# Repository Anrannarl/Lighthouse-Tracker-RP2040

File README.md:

# Lighthouse-Tracker-RP2040
A Lighthouse tracker based on Raspberry Pi Pico.

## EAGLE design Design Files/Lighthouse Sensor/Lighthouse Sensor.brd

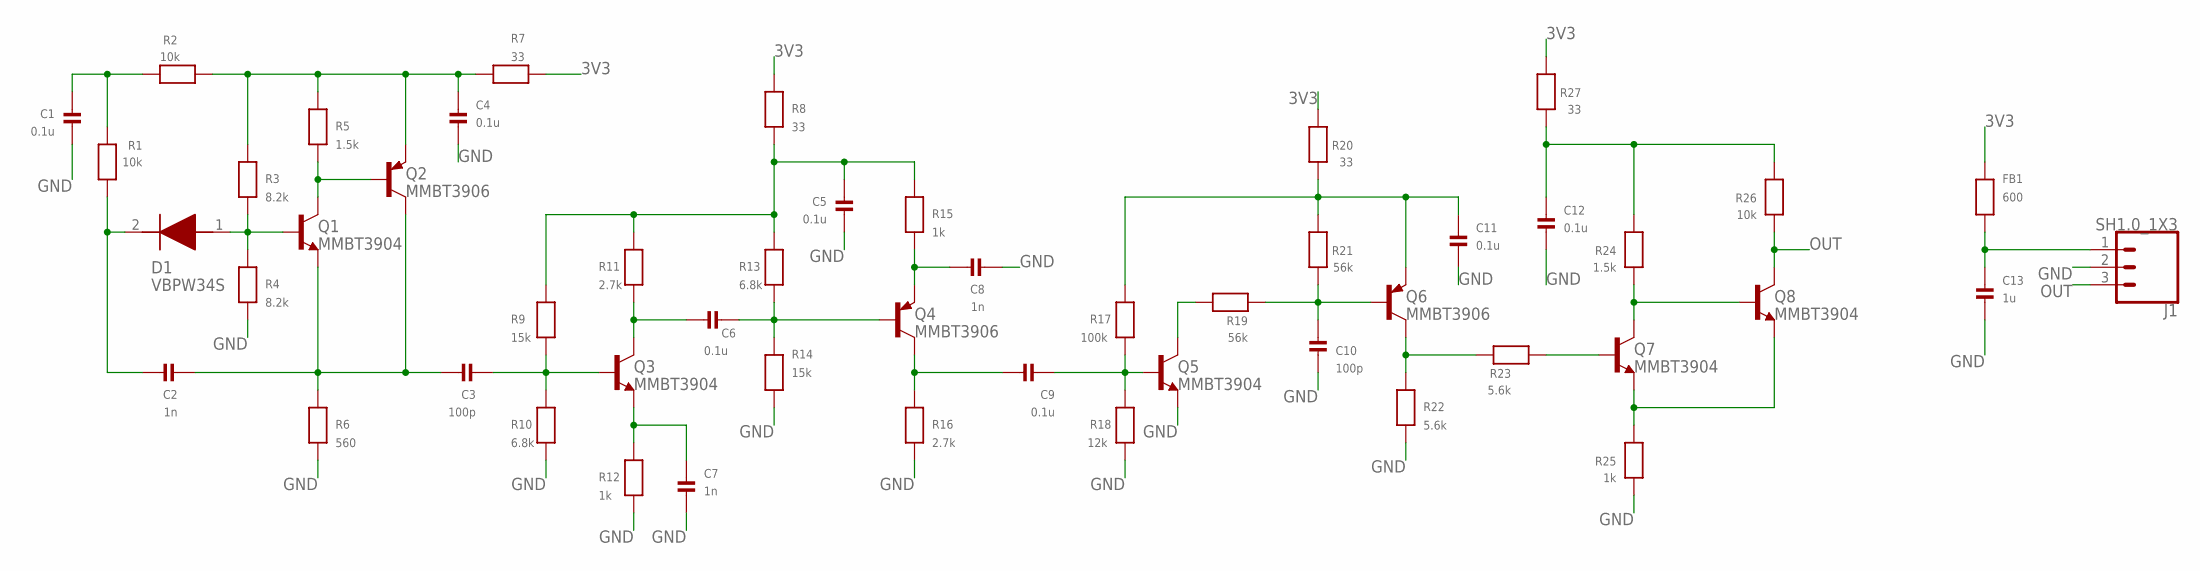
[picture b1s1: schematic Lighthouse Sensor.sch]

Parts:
C1, C4, C5, C6, C9, C11, C12: 0.1u; C0603
C2, C7, C8: 1n; C0603
C3, C10: 100p; C0603
C13: 1u; C0603
D1: VBPW34S
FB1: 600; R0603
J1: SH1.0_1X3; 1X03_1MM_RA
Q1, Q3, Q5, Q7, Q8: MMBT3904; SOT23-BEC
Q2, Q4, Q6: MMBT3906; SOT23-BEC
R1, R2, R26: 10k; R0603
R3, R4: 8.2k; R0603
R5, R24: 1.5k; R0603
R6: 560; R0603
R7, R8, R20, R27: 33; R0603
R9, R14: 15k; R0603
R10, R13: 6.8k; R0603
R11, R16: 2.7k; R0603
R12, R15, R25: 1k; R0603
R17: 100k; R0603
R18: 12k; R0603
R19, R21: 56k; R0603
R22, R23: 5.6k; R0603

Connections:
3V3: FB1.2, R7.2, R8.1, R20.2, R27.2
GND: C1.1, C4.1, C5.2, C7.2, C8.2, C10.1, C11.1, C12.1, C13.1, J1.2, Q5.E, R4.2, R6.2, R10.2, R12.2, R14.2, R16.2, R18.2, R22.1, R25.2
unnamed: C1.2, R1.2, R2.2
unnamed: C2.1, D1.2 (K), R1.1
unnamed: D1.1 (A), Q1.B, R3.2, R4.1
unnamed: C4.2, Q2.E, R2.1, R3.1, R5.1, R7.1
unnamed: Q1.C, Q2.B, R5.2
unnamed: C11.2, Q6.E, R17.1, R20.1, R21.2
unnamed: C5.1, R8.2, R9.1, R11.1, R13.1, R15.1
unnamed: C3.2, Q3.B, R9.2, R10.1
unnamed: C2.2, C3.1, Q1.E, Q2.C, R6.1
unnamed: C6.2, Q4.B, R13.2, R14.1
unnamed: C6.1, Q3.C, R11.2
unnamed: C7.1, Q3.E, R12.1
unnamed: C9.2, Q5.B, R17.2, R18.1
unnamed: C8.1, Q4.E, R15.2
unnamed: C9.1, Q4.C, R16.1
unnamed: Q6.C, R22.2, R23.2
unnamed: C10.2, Q6.B, R19.2, R21.1
unnamed: Q5.C, R19.1
unnamed: Q7.B, R23.1
unnamed: Q7.E, Q8.E, R25.1
unnamed: Q7.C, Q8.B, R24.2
unnamed: C13.2, FB1.1, J1.1
unnamed: C12.2, R24.1, R26.1, R27.1
OUT: J1.3, Q8.C, R26.2

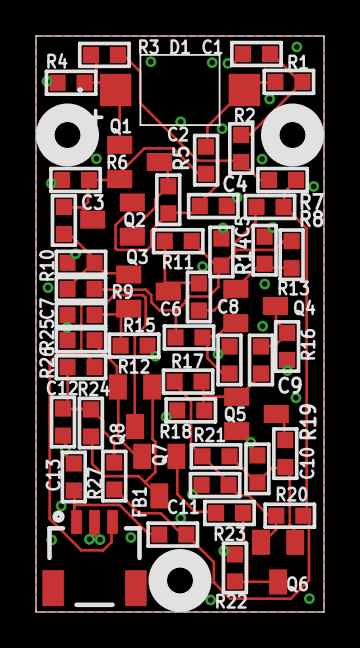
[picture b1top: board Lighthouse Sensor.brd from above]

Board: 2 copper layers, 16.0 x 32.0 mm, 51 parts (0 on the bottom side), 26 nets.

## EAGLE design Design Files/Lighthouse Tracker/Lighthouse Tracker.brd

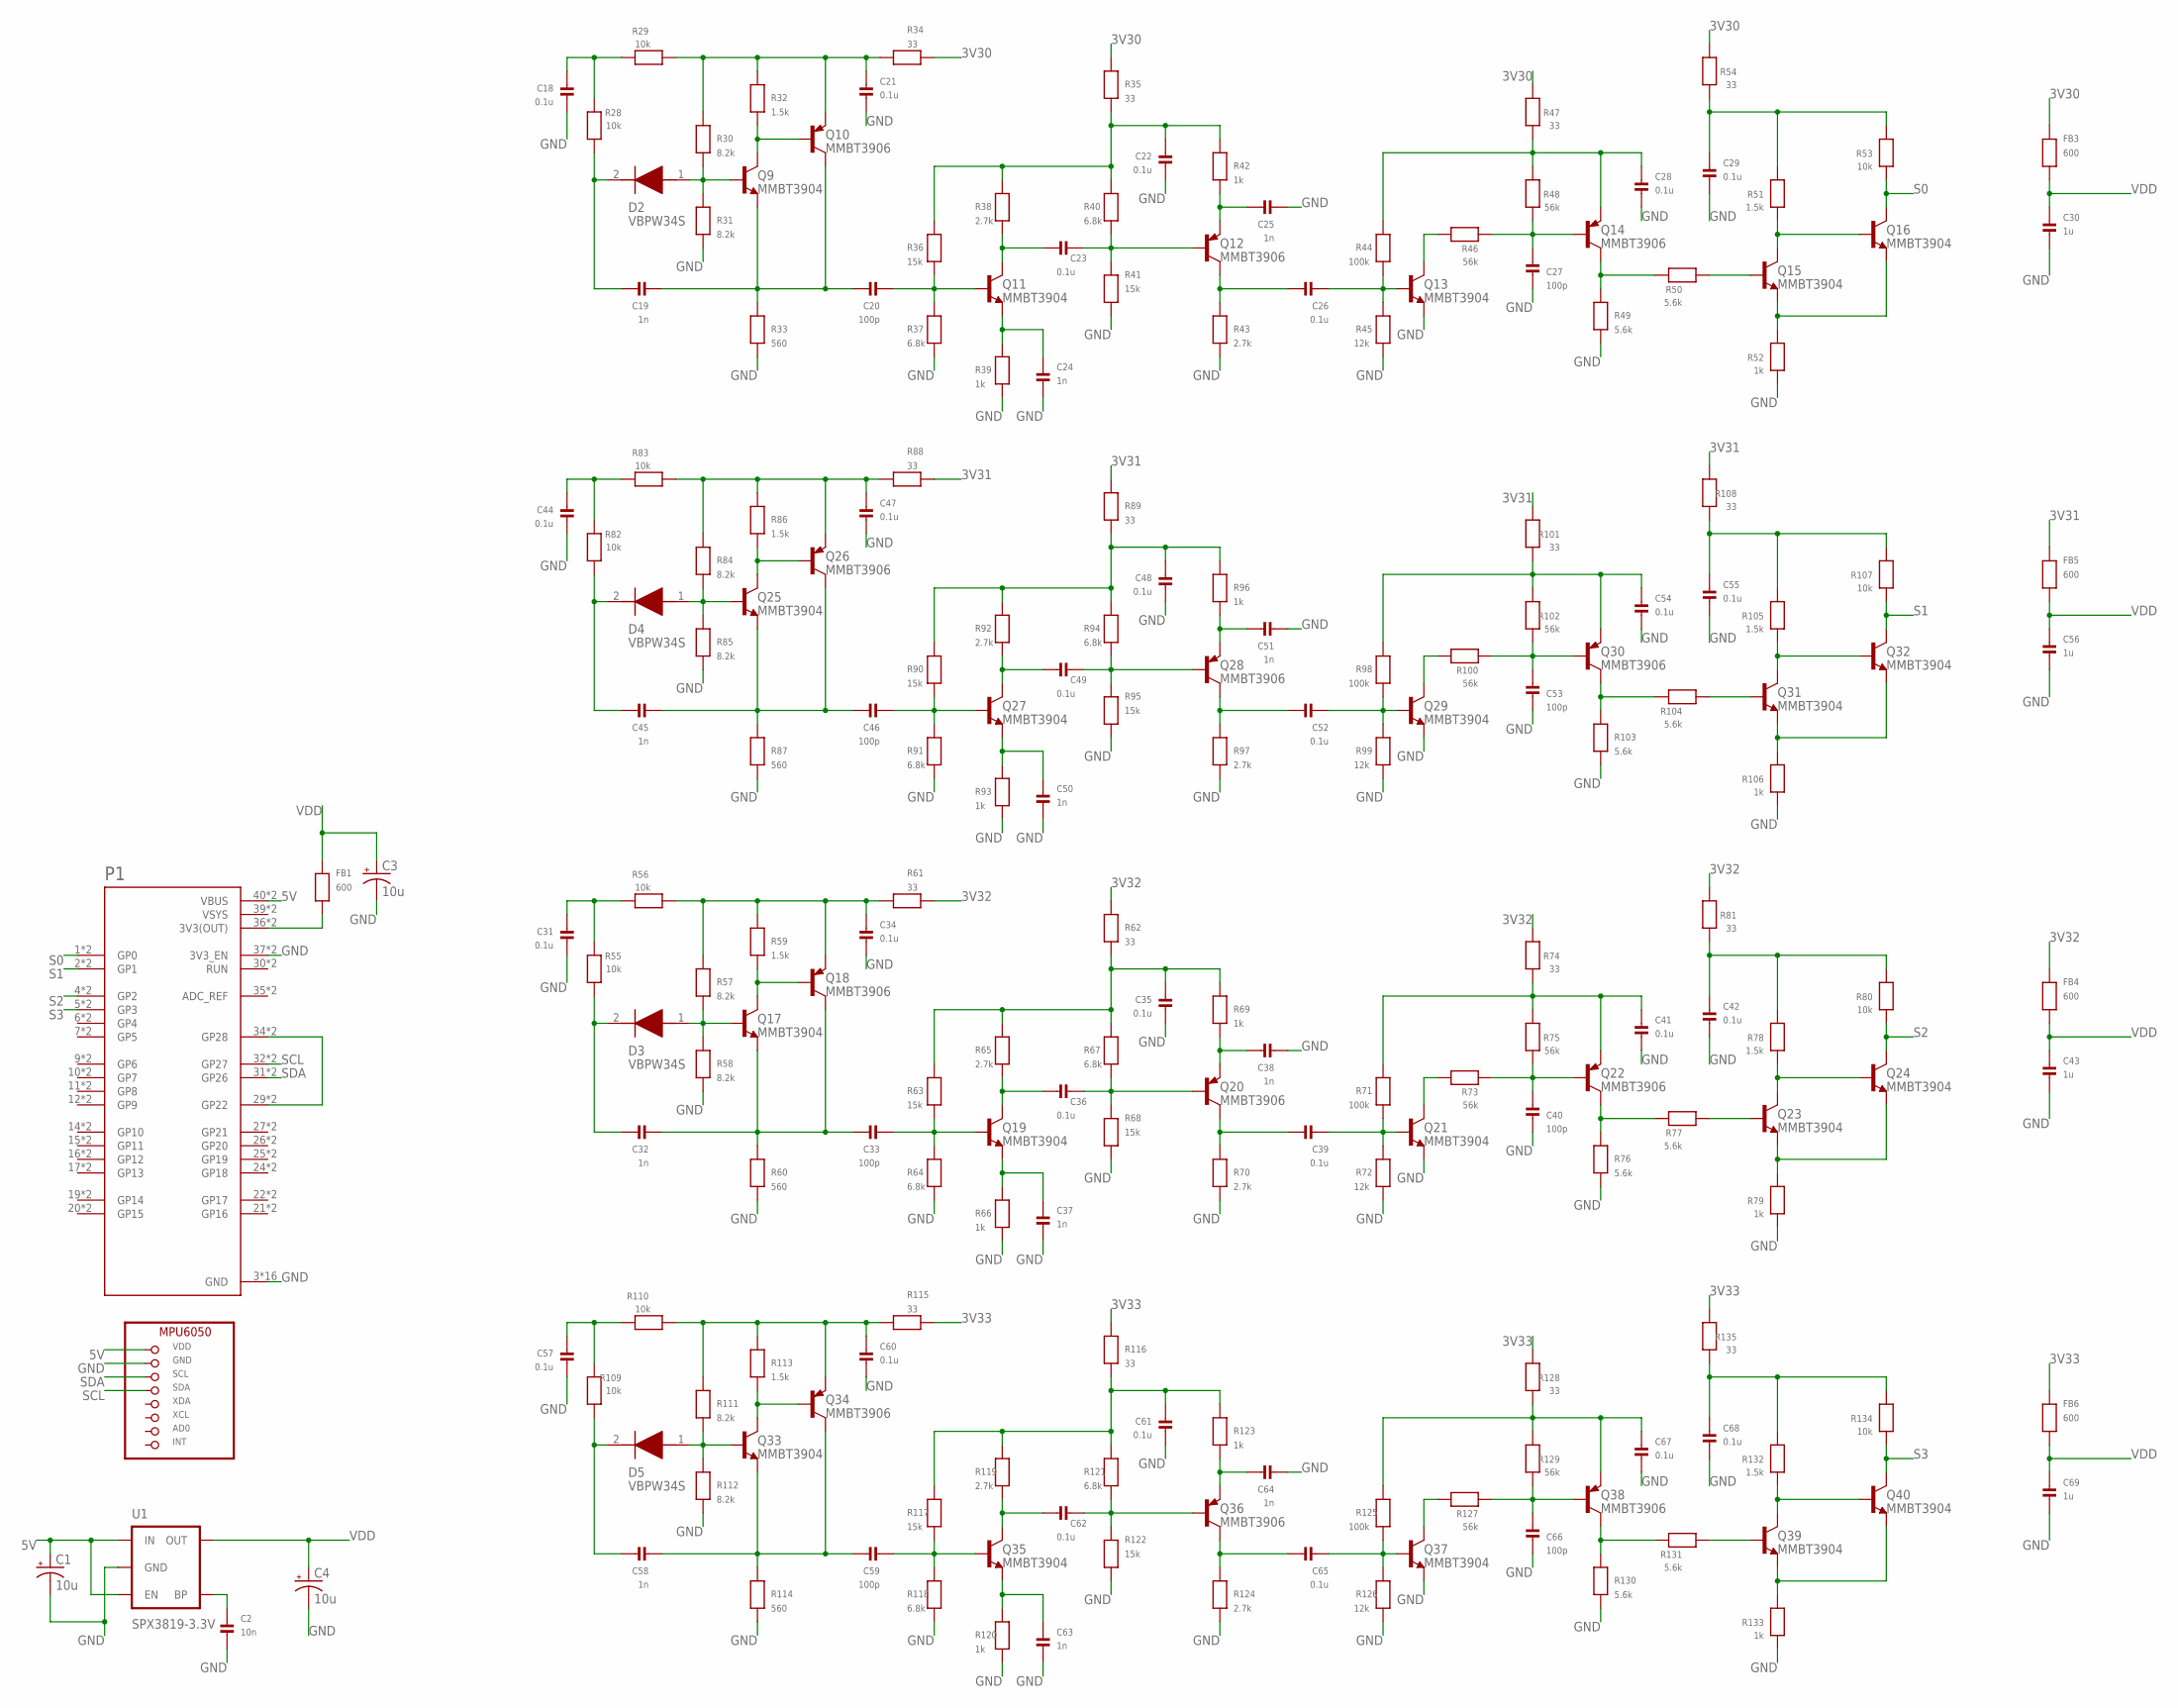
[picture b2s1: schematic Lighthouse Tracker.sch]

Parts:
B1: MPU6050BREAKOUT; MPU6050
C1, C3, C4: 10u; A/3216-18R
C2: 10n; 0603
C18, C21, C22, C23, C26, C28, C29, C31, C34, C35, C36, C39, C41, C42, C44, C47, C48, C49, C52, C54, C55, C57, C60, C61, C62, C65, C67, C68: 0.1u; C0603
C19, C24, C25, C32, C37, C38, C45, C50, C51, C58, C63, C64: 1n; C0603
C20, C27, C33, C40, C46, C53, C59, C66: 100p; C0603
C30, C43, C56, C69: 1u; C0603
D2, D3, D4, D5: VBPW34S
FB1, FB3, FB4, FB5, FB6: 600; R0603
P1: RASPBERRY_PICO-NO_DEBUG; PICO-PKG-NO_DEBUG
Q9, Q11, Q13, Q15, Q16, Q17, Q19, Q21, Q23, Q24, Q25, Q27, Q29, Q31, Q32, Q33, Q35, Q37, Q39, Q40: MMBT3904; SOT23-BEC
Q10, Q12, Q14, Q18, Q20, Q22, Q26, Q28, Q30, Q34, Q36, Q38: MMBT3906; SOT23-BEC
R28, R29, R53, R55, R56, R80, R82, R83, R107, R109, R110, R134: 10k; R0603
R30, R31, R57, R58, R84, R85, R111, R112: 8.2k; R0603
R32, R51, R59, R78, R86, R105, R113, R132: 1.5k; R0603
R33, R60, R87, R114: 560; R0603
R34, R35, R47, R54, R61, R62, R74, R81, R88, R89, R101, R108, R115, R116, R128, R135: 33; R0603
R36, R41, R63, R68, R90, R95, R117, R122: 15k; R0603
R37, R40, R64, R67, R91, R94, R118, R121: 6.8k; R0603
R38, R43, R65, R70, R92, R97, R119, R124: 2.7k; R0603
R39, R42, R52, R66, R69, R79, R93, R96, R106, R120, R123, R133: 1k; R0603
R44, R71, R98, R125: 100k; R0603
R45, R72, R99, R126: 12k; R0603
R46, R48, R73, R75, R100, R102, R127, R129: 56k; R0603
R49, R50, R76, R77, R103, R104, R130, R131: 5.6k; R0603
U1: SPX3819-3.3V; SOT23-5

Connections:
3V30: FB3.2, R34.2, R35.1, R47.2, R54.2
3V31: FB5.2, R88.2, R89.1, R101.2, R108.2
3V32: FB4.2, R61.2, R62.1, R74.2, R81.2
3V33: FB6.2, R115.2, R116.1, R128.2, R135.2
5V: B1.VDD, C1.+, P1.40 (VBUS), P1.P$40 (VBUS), U1.1 (IN), U1.3 (EN)
GND: B1.GND, C1.-, C2.2, C3.-, C4.-, C18.1, C21.1, C22.2, C24.2, C25.2, C27.1, C28.1, C29.1, C30.1, C31.1, C34.1, C35.2, C37.2, C38.2, C40.1, C41.1, C42.1, C43.1, C44.1, C47.1, C48.2, C50.2, C51.2, C53.1, C54.1, C55.1, C56.1, C57.1, C60.1, C61.2, C63.2, C64.2, C66.1, C67.1, C68.1, C69.1, P1.3 (GND), P1.8 (GND), P1.13 (GND), P1.18 (GND), P1.23 (GND), P1.28 (GND), P1.33 (GND), P1.37 (3V3_EN), P1.38 (GND), P1.P$3 (GND), P1.P$8 (GND), P1.P$13 (GND), P1.P$18 (GND), P1.P$23 (GND), P1.P$28 (GND), P1.P$33 (GND), P1.P$37 (3V3_EN), P1.P$38 (GND), Q13.E, Q21.E, Q29.E, Q37.E, R31.2, R33.2, R37.2, R39.2, R41.2, R43.2, R45.2, R49.1, R52.2, R58.2, R60.2, R64.2, R66.2, R68.2, R70.2, R72.2, R76.1, R79.2, R85.2, R87.2, R91.2, R93.2, R95.2, R97.2, R99.2, R103.1, R106.2, R112.2, R114.2, R118.2, R120.2, R122.2, R124.2, R126.2, R130.1, R133.2, U1.2 (GND)
unnamed: C2.1, U1.4 (BP)
unnamed: FB1.1, P1.36 (3V3(OUT)), P1.P$36 (3V3(OUT))
unnamed: P1.29 (GP22), P1.34 (GP28), P1.P$29 (GP22), P1.P$34 (GP28)
unnamed: C18.2, R28.2, R29.2
unnamed: C19.1, D2.2 (K), R28.1
unnamed: D2.1 (A), Q9.B, R30.2, R31.1
unnamed: C21.2, Q10.E, R29.1, R30.1, R32.1, R34.1
unnamed: Q9.C, Q10.B, R32.2
unnamed: C19.2, C20.1, Q9.E, Q10.C, R33.1
unnamed: C22.1, R35.2, R36.1, R38.1, R40.1, R42.1
unnamed: C20.2, Q11.B, R36.2, R37.1
unnamed: C23.1, Q11.C, R38.2
unnamed: C24.1, Q11.E, R39.1
unnamed: C23.2, Q12.B, R40.2, R41.1
unnamed: C25.1, Q12.E, R42.2
unnamed: C26.1, Q12.C, R43.1
unnamed: C26.2, Q13.B, R44.2, R45.1
unnamed: C28.2, Q14.E, R44.1, R47.1, R48.2
unnamed: C27.2, Q14.B, R46.2, R48.1
unnamed: Q13.C, R46.1
unnamed: Q14.C, R49.2, R50.2
unnamed: Q15.B, R50.1
unnamed: Q15.E, Q16.E, R52.1
unnamed: Q15.C, Q16.B, R51.2
unnamed: C29.2, R51.1, R53.1, R54.1
unnamed: C31.2, R55.2, R56.2
unnamed: C32.1, D3.2 (K), R55.1
unnamed: D3.1 (A), Q17.B, R57.2, R58.1
unnamed: C34.2, Q18.E, R56.1, R57.1, R59.1, R61.1
unnamed: Q17.C, Q18.B, R59.2
unnamed: C32.2, C33.1, Q17.E, Q18.C, R60.1
unnamed: C35.1, R62.2, R63.1, R65.1, R67.1, R69.1
unnamed: C33.2, Q19.B, R63.2, R64.1
unnamed: C36.1, Q19.C, R65.2
unnamed: C37.1, Q19.E, R66.1
unnamed: C36.2, Q20.B, R67.2, R68.1
unnamed: C38.1, Q20.E, R69.2
unnamed: C39.1, Q20.C, R70.1
unnamed: C39.2, Q21.B, R71.2, R72.1
unnamed: C41.2, Q22.E, R71.1, R74.1, R75.2
unnamed: C40.2, Q22.B, R73.2, R75.1
unnamed: Q21.C, R73.1
unnamed: Q22.C, R76.2, R77.2
unnamed: Q23.B, R77.1
unnamed: Q23.E, Q24.E, R79.1
unnamed: Q23.C, Q24.B, R78.2
unnamed: C42.2, R78.1, R80.1, R81.1
unnamed: C44.2, R82.2, R83.2
unnamed: C45.1, D4.2 (K), R82.1
unnamed: D4.1 (A), Q25.B, R84.2, R85.1
unnamed: C47.2, Q26.E, R83.1, R84.1, R86.1, R88.1
unnamed: Q25.C, Q26.B, R86.2
unnamed: C45.2, C46.1, Q25.E, Q26.C, R87.1
unnamed: C48.1, R89.2, R90.1, R92.1, R94.1, R96.1
unnamed: C46.2, Q27.B, R90.2, R91.1
unnamed: C49.1, Q27.C, R92.2
unnamed: C50.1, Q27.E, R93.1
unnamed: C49.2, Q28.B, R94.2, R95.1
unnamed: C51.1, Q28.E, R96.2
unnamed: C52.1, Q28.C, R97.1
unnamed: C52.2, Q29.B, R98.2, R99.1
unnamed: C54.2, Q30.E, R98.1, R101.1, R102.2
unnamed: C53.2, Q30.B, R100.2, R102.1
unnamed: Q29.C, R100.1
unnamed: Q30.C, R103.2, R104.2
unnamed: Q31.B, R104.1
unnamed: Q31.E, Q32.E, R106.1
unnamed: Q31.C, Q32.B, R105.2
unnamed: C55.2, R105.1, R107.1, R108.1
unnamed: C57.2, R109.2, R110.2
unnamed: C58.1, D5.2 (K), R109.1
unnamed: D5.1 (A), Q33.B, R111.2, R112.1
unnamed: C60.2, Q34.E, R110.1, R111.1, R113.1, R115.1
unnamed: Q33.C, Q34.B, R113.2
unnamed: C58.2, C59.1, Q33.E, Q34.C, R114.1
unnamed: C61.1, R116.2, R117.1, R119.1, R121.1, R123.1
unnamed: C59.2, Q35.B, R117.2, R118.1
unnamed: C62.1, Q35.C, R119.2
unnamed: C63.1, Q35.E, R120.1
unnamed: C62.2, Q36.B, R121.2, R122.1
unnamed: C64.1, Q36.E, R123.2
unnamed: C65.1, Q36.C, R124.1
unnamed: C65.2, Q37.B, R125.2, R126.1
unnamed: C67.2, Q38.E, R125.1, R128.1, R129.2
unnamed: C66.2, Q38.B, R127.2, R129.1
unnamed: Q37.C, R127.1
unnamed: Q38.C, R130.2, R131.2
unnamed: Q39.B, R131.1
unnamed: Q39.E, Q40.E, R133.1
unnamed: Q39.C, Q40.B, R132.2
unnamed: C68.2, R132.1, R134.1, R135.1
S0: P1.1 (GP0), P1.P$1 (GP0), Q16.C, R53.2
S1: P1.2 (GP1), P1.P$2 (GP1), Q32.C, R107.2
S2: P1.4 (GP2), P1.P$4 (GP2), Q24.C, R80.2
S3: P1.5 (GP3), P1.P$5 (GP3), Q40.C, R134.2
SCL: B1.SDA, P1.32 (GP27), P1.P$32 (GP27)
SDA: B1.SCL, P1.31 (GP26), P1.P$31 (GP26)
VDD: C3.+, C4.+, C30.2, C43.2, C56.2, C69.2, FB1.2, FB3.1, FB4.1, FB5.1, FB6.1, U1.5 (OUT)
VSYS: P1.39 (VSYS), P1.P$39 (VSYS)

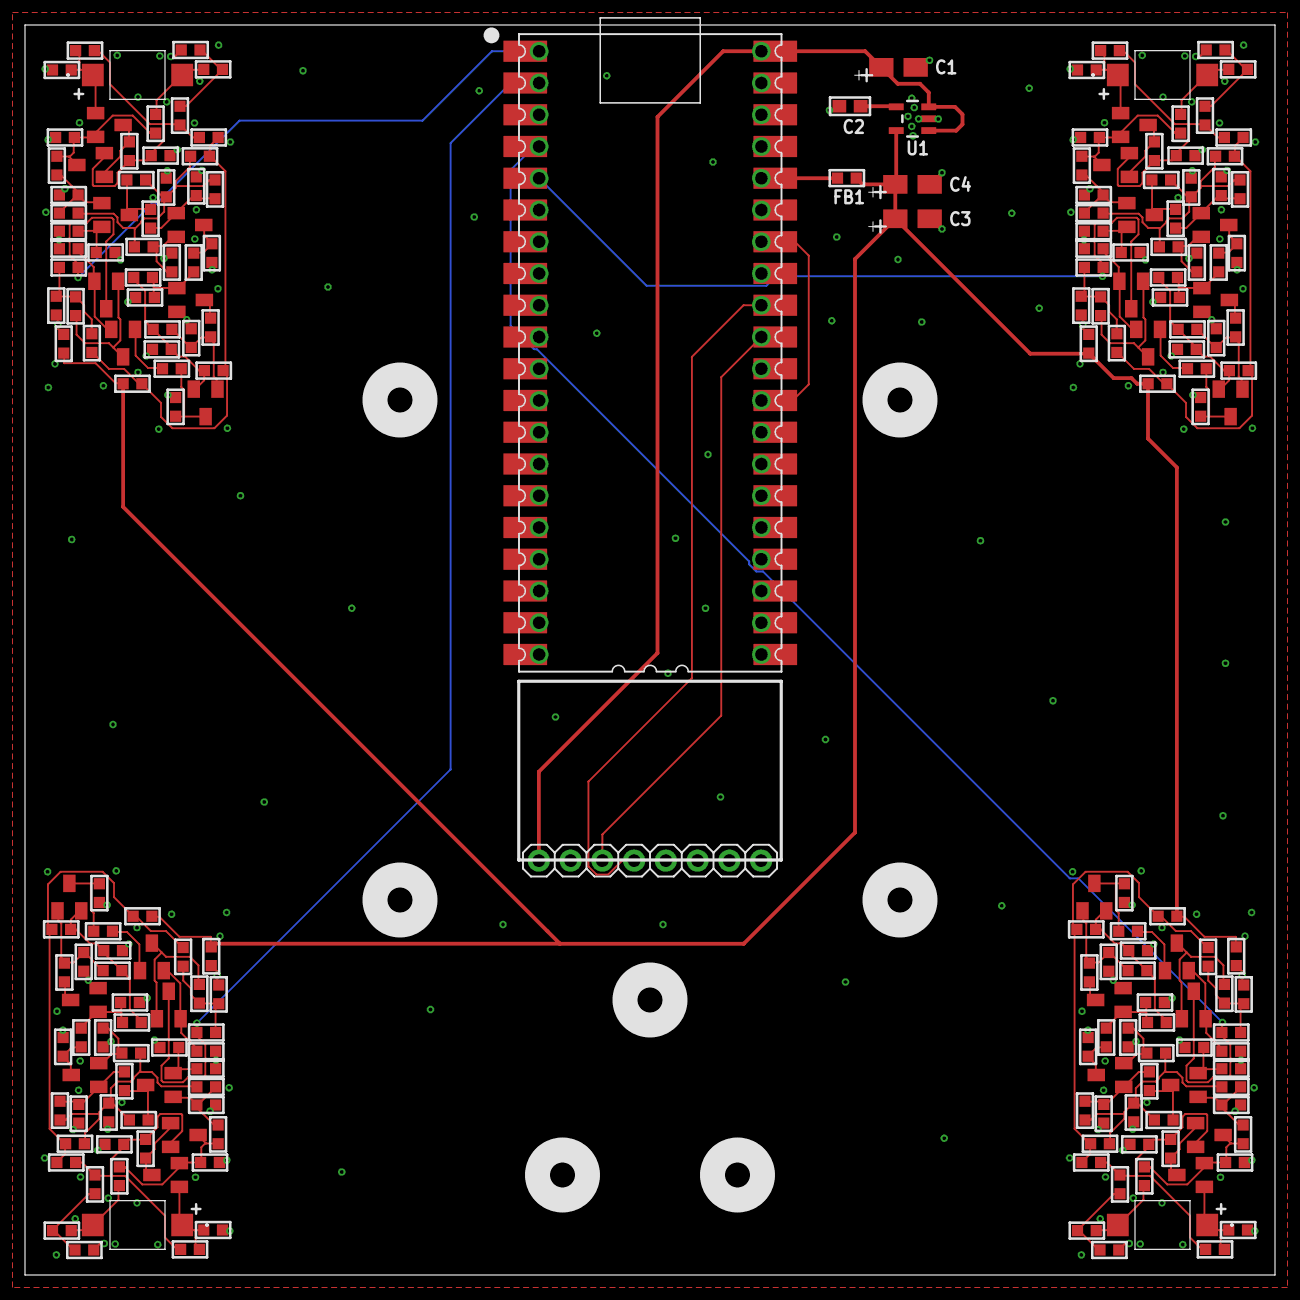
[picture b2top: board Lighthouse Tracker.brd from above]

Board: 2 copper layers, 100.0 x 100.0 mm, 208 parts (0 on the bottom side), 105 nets.

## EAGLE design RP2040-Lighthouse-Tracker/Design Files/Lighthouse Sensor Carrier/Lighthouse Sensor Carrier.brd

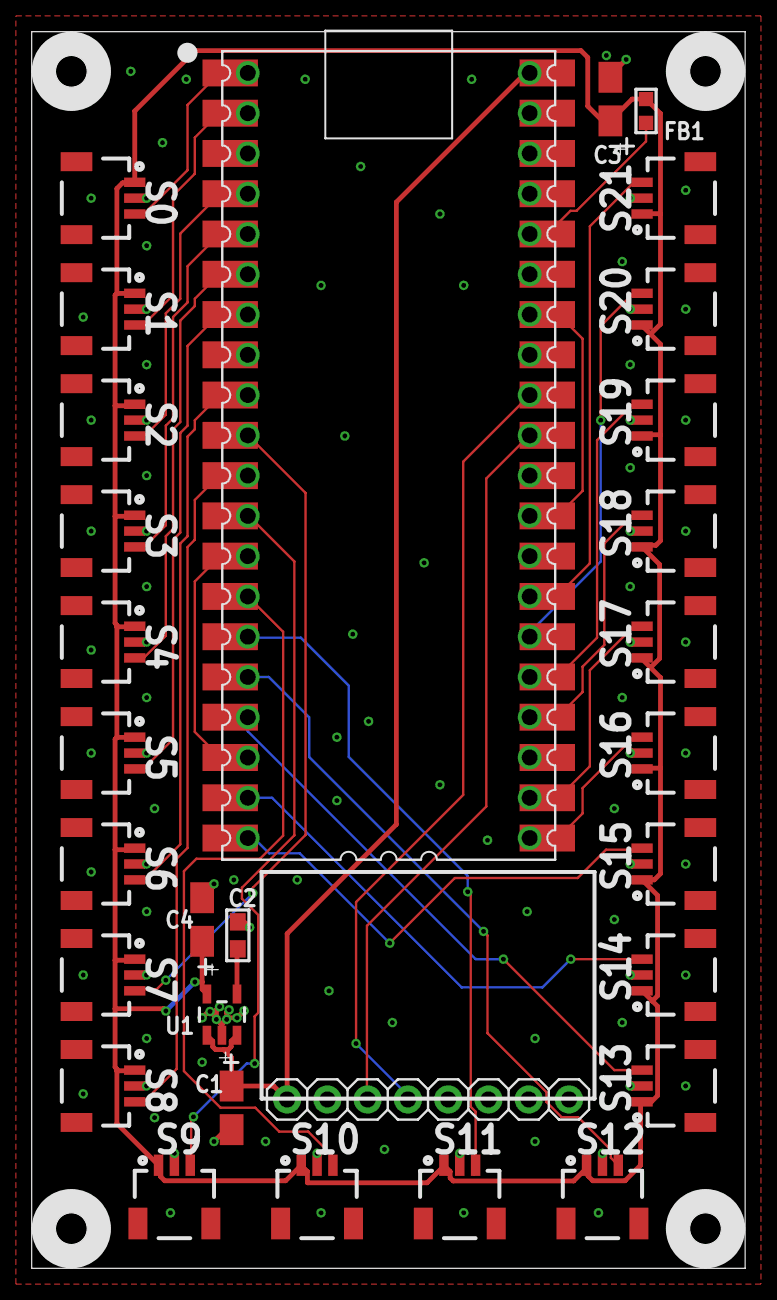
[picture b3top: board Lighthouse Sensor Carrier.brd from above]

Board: 2 copper layers, 45.0 x 78.0 mm, 30 parts (0 on the bottom side), 31 nets.

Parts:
C1, C3, C4: 10u; A/3216-18R
C2: 10n; 0603
FB1: 600; R0603
P1: PICO-PKG-NO_DEBUG
S0, S1, S2, S3, S4, S5, S6, S7, S8, S9, S10, S11, S12, S13, S14, S15, S16, S17, S18, S19, S20, S21: SH1.0_1X3; 1X03_1MM_RA
U1: SPX3819-3.3V; SOT23-5
U$1: MPU6050BREAKOUT; MPU6050

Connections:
3V3: C3.+, C4.+, FB1.2, S0.1, S1.1, S2.1, S3.1, S4.1, S5.1, S6.1, S7.1, S8.1, S9.1, S10.1, S11.1, S12.1, S13.1, S14.1, S15.1, S16.1, S17.1, S18.1, S19.1, S20.1, S21.1, U1.5
5V: C1.+, P1.40, P1.P$40, U1.1, U1.3, U$1.VDD
GND: C1.-, C2.2, C3.-, C4.-, P1.3, P1.8, P1.13, P1.18, P1.23, P1.28, P1.33, P1.37, P1.38, P1.P$3, P1.P$8, P1.P$13, P1.P$18, P1.P$23, P1.P$28, P1.P$33, P1.P$37, P1.P$38, S0.2, S1.2, S2.2, S3.2, S4.2, S5.2, S6.2, S7.2, S8.2, S9.2, S10.2, S11.2, S12.2, S13.2, S14.2, S15.2, S16.2, S17.2, S18.2, S19.2, S20.2, S21.2, U1.2, U$1.GND
unnamed: C2.1, U1.4
unnamed: FB1.1, P1.36, P1.P$36
unnamed: P1.29, P1.34, P1.P$29, P1.P$34
S0: P1.1, P1.P$1, S0.3
S1: P1.2, P1.P$2, S1.3
S2: P1.4, P1.P$4, S2.3
S3: P1.5, P1.P$5, S3.3
S4: P1.6, P1.P$6, S4.3
S5: P1.7, P1.P$7, S5.3
S6: P1.9, P1.P$9, S6.3
S7: P1.10, P1.P$10, S7.3
S8: P1.11, P1.P$11, S8.3
S9: P1.12, P1.P$12, S9.3
S10: P1.14, P1.P$14, S10.3
S11: P1.15, P1.P$15, S11.3
S12: P1.16, P1.P$16, S12.3
S13: P1.17, P1.P$17, S13.3
S14: P1.19, P1.P$19, S14.3
S15: P1.20, P1.P$20, S15.3
S16: P1.21, P1.P$21, S16.3
S17: P1.22, P1.P$22, S17.3
S18: P1.24, P1.P$24, S18.3
S19: P1.25, P1.P$25, S19.3
S20: P1.26, P1.P$26, S20.3
S21: P1.27, P1.P$27, S21.3
SCL: P1.32, P1.P$32, U$1.SDA
SDA: P1.31, P1.P$31, U$1.SCL
VSYS: P1.39, P1.P$39

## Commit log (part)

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2023-05-16 Create LICENSE
